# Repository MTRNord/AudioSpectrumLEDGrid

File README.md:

# AudioSpectrumLEDGrid
A PCB and Software to convert an audio mono signal into a grid made of LEDs.

## WARNING: SOFTWARE NOT READY!

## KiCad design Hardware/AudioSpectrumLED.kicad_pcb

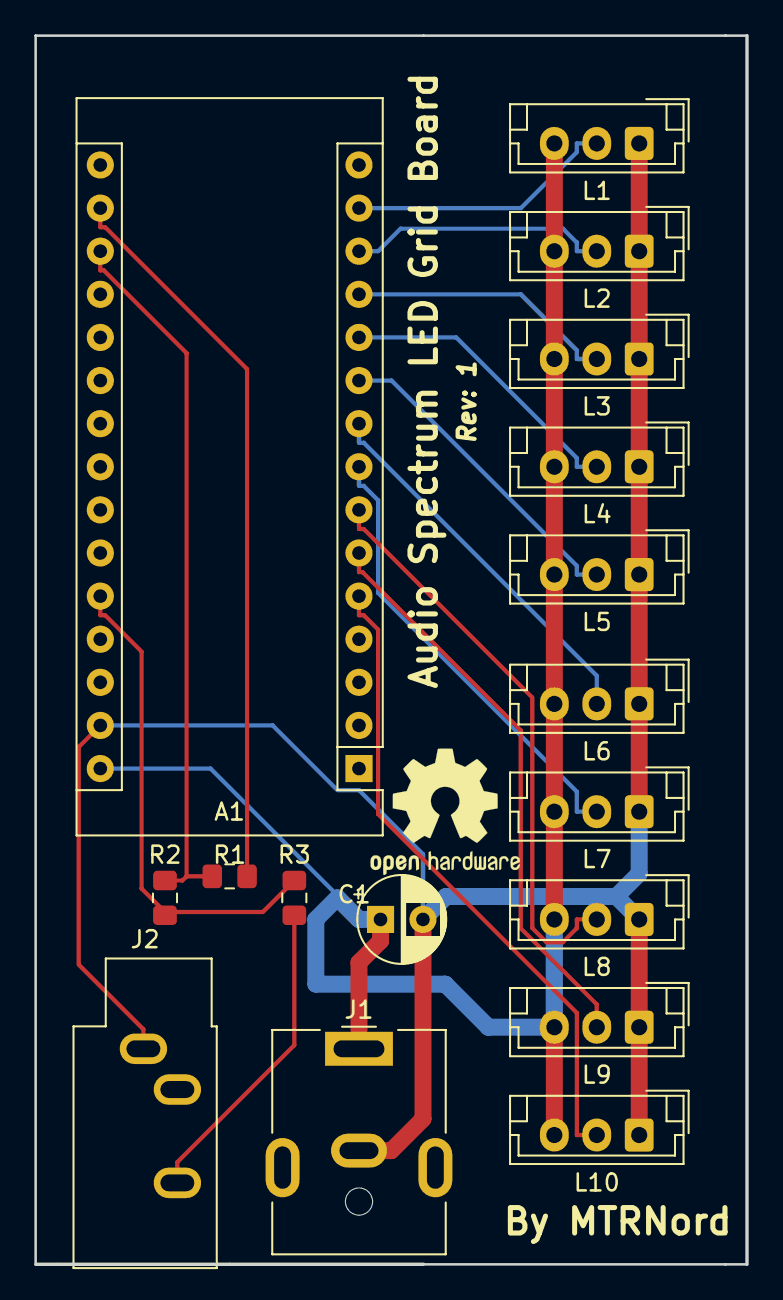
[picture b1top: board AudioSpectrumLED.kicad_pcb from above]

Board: 2 copper layers, 41.9 x 72.4 mm, 17 parts (0 on the bottom side), 16 nets.

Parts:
A1: Arduino_Nano_v3.x; Arduino_Nano
C1: CP; CP_Radial_D5.0mm_P2.50mm
J1: Barrel_Jack; BarrelJack_CUI_PJ-063AH_Horizontal
J2: AudioJack3; Jack_3.5mm_CUI_SJ1-3533NG_Horizontal
L1, L2, L3, L4, L5, L6, L7, L8, L9, L10: Led_Strip_Connector; JST_EH_B03B-EH-A_1x03_P2.50mm_Vertical
R1: 4,7 k; R_0805_2012Metric_Pad1.15x1.40mm_HandSolder
R2, R3: 1,8 k; R_0805_2012Metric_Pad1.15x1.40mm_HandSolder

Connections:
/LED_SIGNAL_1: A1.14, L1.2
/LED_SIGNAL_2: A1.13, L2.2
/LED_SIGNAL_3: A1.12, L3.2
/LED_SIGNAL_4: A1.11, L4.2
/LED_SIGNAL_5: A1.10, L5.2
/LED_SIGNAL_6: A1.9, L6.2
/LED_SIGNAL_7: A1.8, L7.2
/LED_SIGNAL_8: A1.7, L8.2
/LED_SIGNAL_9: A1.6, L9.2
/LED_SIGNAL_10: A1.5, L10.2
GND: A1.29, C1.2, J1.2, J2.S, L1.1, L2.1, L3.1, L4.1, L5.1, L6.1, L7.1, L8.1, L9.1, L10.1
unnamed: A1.17, R1.1
unnamed: A1.18, R1.2, R2.1
unnamed: A1.26, R2.2, R3.1
unnamed: J2.R, R3.2
VCC: A1.30, C1.1, J1.1, L1.3, L2.3, L3.3, L4.3, L5.3, L6.3, L7.3, L8.3, L9.3, L10.3

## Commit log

2019-02-02 Initial PCB Commit
2019-02-02 Update Image and update Readme
